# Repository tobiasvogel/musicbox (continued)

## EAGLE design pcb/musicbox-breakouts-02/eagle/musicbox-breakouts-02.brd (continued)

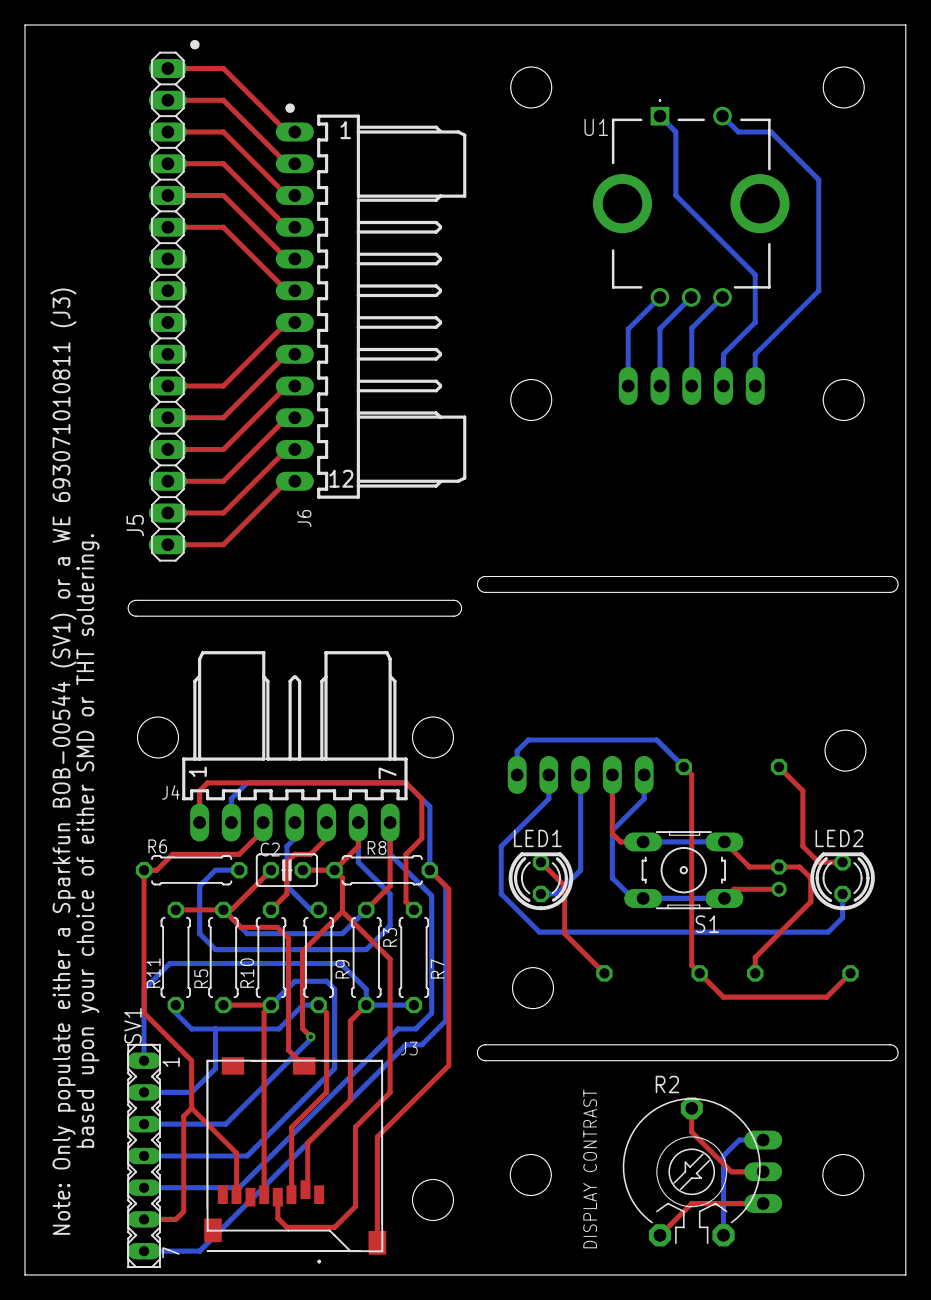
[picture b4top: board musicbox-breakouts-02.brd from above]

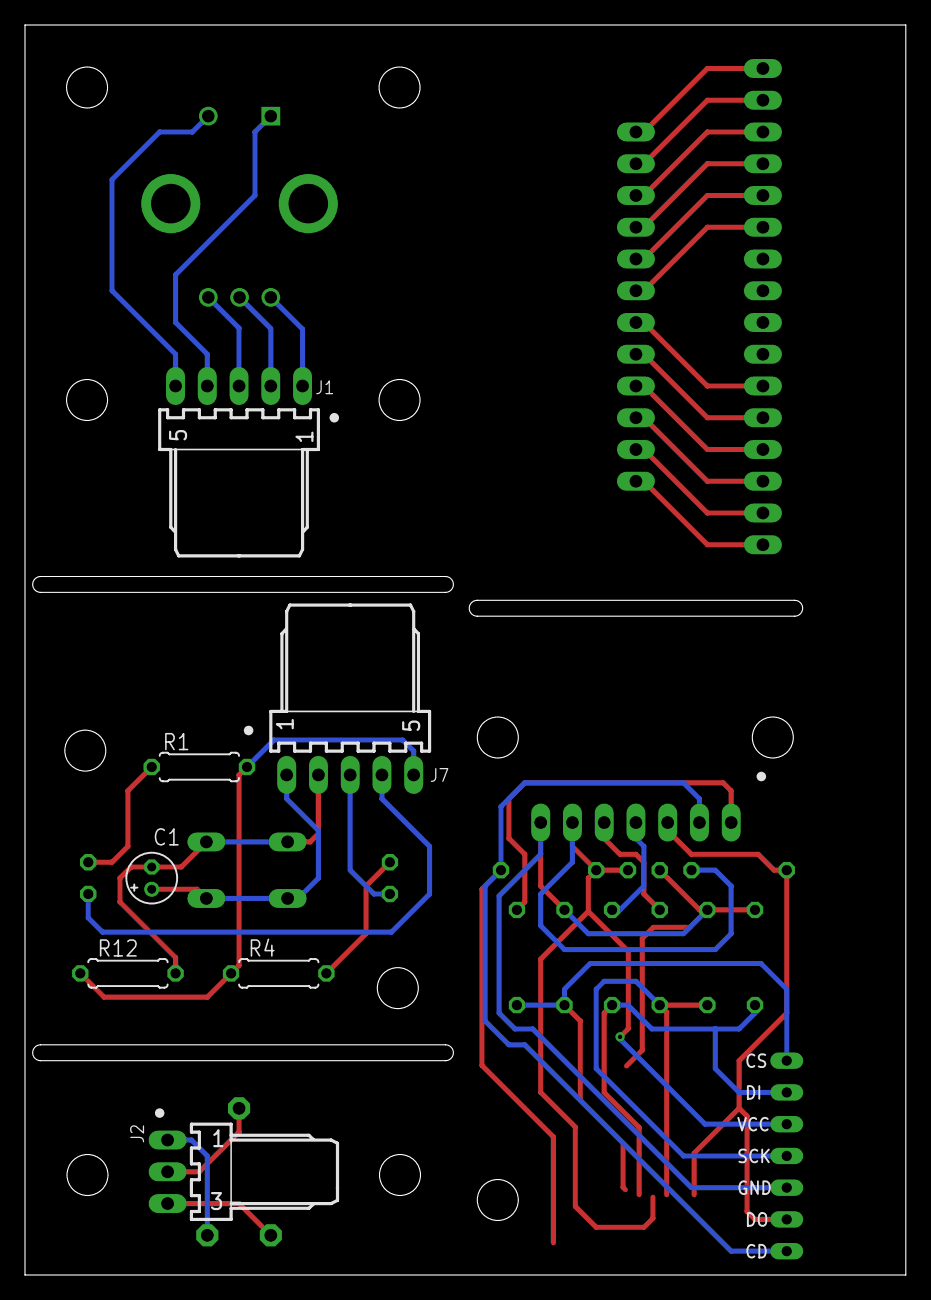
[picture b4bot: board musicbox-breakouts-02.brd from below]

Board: 2 copper layers, 70.5 x 100.0 mm, 26 parts (7 on the bottom side), 37 nets.

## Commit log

2022-07-05 added convenience functions (copy/paste)
2022-07-05 added function to select servo order and used <fieldset>-tags for styling
2022-07-05 added some css styling
2022-07-05 added c99 flag, renamed using capital 'M'
2022-07-05 added -std=c99 flag
2022-07-05 added eagle cad files
2022-07-05 removed midimoshi.htm
2022-07-07 added gerber files
